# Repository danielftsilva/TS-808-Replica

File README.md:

<h1>TS-808 Replica Project</h1>

<h2>Description</h2>

This repository details my research, design, assembly, and testing of a replica of the iconic TS-808 distortion pedal.

<h2>🎸 Project Summary:</h2>

<b>Research:</b> Studied the original TS-808 design and gathered all necessary information.

<b>Design:</b> Created PCB schematics and layout using KiCad.

<b>Assembly:</b> Purchased components and assembled the PCB.

<b>Testing:</b> Tested to ensure functionality (the most fun part).

<b>Documentation:</b> Photos and documents of every step of the process.

<h2>⚡ Implementation Details:</h2>

<b>From Reference Schematic to PCB:</b>

- The design is rooted in the [reference schematic](https://github.com/danielftsilva/TS-808-Replica/blob/main/KiCad%20Project/ts-808_original%20reference_circuit.jpg) for the Ibanez TS-808 circuit, capturing the preamp, diode clipping, and tone control sections. This schematic outlines the signal path - from the initial buffering of the input signal through the op-amp stages to the final output drive.

- The "heart" of this circuit is the [RC4558](https://www.ti.com/lit/ds/symlink/rc4558.pdf?ts=1740038954763&ref_url=https%253A%252F%252Fwww.google.com%252F), a dual OP-AMP. It handles both the input buffering and the overdrive stages. It's low-noise gives you a warm, smooth distortion (the main and sought-out characteristic of this pedal!). Also, the dual configuration allows one section to amplify the signal while the other handles its tone.

- Here you can see the [final circuit schematic](https://github.com/danielftsilva/TS-808-Replica/blob/main/KiCad%20Project/Main%20Circuit.png).

<!-- modifications -->
<!-- There were a few modifications done on the circuit, namely:

1. Asymmetric clipping: two diodes placed in series (D1 and D2) introduce asymmetric clipping and produce a more "tube-like" distortion with a more dynamic response;

2. Clipper change: a lever switch (SPST) allows selection between different clipping devices - in this case between silicon diodes (1N914) and regular red LEDs. This gives us two distortion textures in the same circuit, providing more flexibility in shaping the pedal's sound;

3. AMZ Fat Modification

Change: A switch is added to bypass capacitor C3.

Impact: Increases boost and enhances bass response, resulting in a fuller and richer tone.

4. Keeley 808 Reissue Modifications

Changes:

Replace R6 (4.7kΩ) with a 2.4kΩ resistor.

Replace R7 (51kΩ) with a 20kΩ resistor.

Replace C3 (0.047µF) with a 0.1µF capacitor.

Replace C9 (0.22µF) with a 0.18µF capacitor.

Impact: Improves bass response and increases distortion at higher drive settings, enhancing the pedal's versatility.

5. Diode Lift Modification

Change: Uses an on-off-on SPDT toggle switch for the diode clipper selector, allowing diode clippers to be lifted from the feedback loop.

Impact: Enables the pedal to function as a clean booster when the diodes are lifted. At high drive settings, this may introduce a more aggressive, raw distortion.

6. Expensive Boutique Modifications

Changes:

Implements diode switching with a diode lift option.

Applies asymmetric clipping modification.

Replaces the Drive potentiometer with a 1MΩ logarithmic pot.

Impact: Aims to replicate high-end boutique overdrive pedals, providing increased gain and a unique tonal character.

Build Information

The project is built on a PCB based on the original TS-808 schematic, with additional wiring for the modifications.

High-quality components were used to maintain signal integrity and reliability.

The modifications were inspired by well-known guitar pedal modders and adapted to suit a wide range of playing styles. -->
<!-- -->

- The [placement afterwards](https://github.com/danielftsilva/TS-808-Replica/blob/main/KiCad%20Project/Layout/Placement_2.png) was super simple and straighforward - just had to pay attention to the distance between the components (I used a [1mm track width](https://github.com/danielftsilva/TS-808-Replica/blob/main/KiCad%20Project/Layout/tracks_2.png) as it was more than enough for this project).

- This PCB is comprised of a simple 2-layer stackup ([main design rules here](https://github.com/danielftsilva/TS-808-Replica/blob/main/KiCad%20Project/production/JLCPCB_KiCad_board_setup_1.png)) - the components occupy the top layer (even though they are all THT). Therefore, in order to not this layer, all the tracks were routed on the bottom layer, which can be seen here in the [final layout](https://github.com/danielftsilva/TS-808-Replica/blob/main/KiCad%20Project/Layout/Layout.png).

<b>Component Selection and Soldering:</b>

- The components selected are listed in the [BOM file](https://github.com/danielftsilva/TS-808-Replica/blob/main/BOM/ts_808_generated_BOM.xlsx).

- The [PCB](https://github.com/danielftsilva/TS-808-Replica/blob/main/Assembly/PCB_unpopulated.jpg) was ordered from [JLC PCB](https://github.com/danielftsilva/TS-808-Replica/blob/main/KiCad%20Project/production/JLC_PCB_order.png) and it measures 75.00mm x 52.00mm. It was intended to fit inside a 127.00mm x 76.250mm [Hammond enclosure](https://eu.mouser.com/ProductDetail/Hammond-Manufacturing/1411NU?qs=k5YXvLLCsLFkprr1MgbOww%3D%3D).

- Here you can see the [final populated PCB](https://github.com/danielftsilva/TS-808-Replica/blob/main/Assembly/PCB_populated.jpg).

<b>Testing and Troubleshooting:</b>

- I started by assembling the populated PCB and external components with the help of a breadboard. Then, I powered up the pedal to check for proper voltage levels and continuity across the circuit using a multimeter.

- I used [this troubleshooting guide](https://github.com/danielftsilva/TS-808-Replica/blob/main/Tests/TROUBLESHOOTING%20CHART.jpg) for my [check](https://github.com/danielftsilva/TS-808-Replica/blob/main/Tests/schematic%20component%20test%20check.png). It is very useful to diagnose common issues like misoriented components or cold solder joints.

- *Note: if you encounter audible noise on this breadboard setup, do not worry too much - it is much likely due to the lack of proper grounding. Also, using somewhat long prototyping cables like I used can help pickup random noise! This should be solved once you assemble everything inside the metal enclosure.*

- Here is [video footage of me testing the complete circuit](https://github.com/danielftsilva/TS-808-Replica/blob/main/Tests/Test.mov), using a breadboard - troubleshooting phase.

- Here you can see the [final assembled pedal turned on](https://github.com/danielftsilva/TS-808-Replica/blob/main/Tests/Pedal_ON_2.jpeg), using a 9V, 1A AC/DC adapter.

- and video footage (Test.mov), ensures every aspect of the build is verified.

<b>Mechanical Integration:</b>

- Once populated, the PCB was mounted within the pedal's enclosure. Let the importance of proper mechanical support be stressed! This is to minimize vibration and potential interference.

- The external components - jacks, switches and potentiometers - [were then connected](https://github.com/danielftsilva/TS-808-Replica/blob/main/Assembly/Pedal_assembled_1.jpeg). Wire routing is crucial to prevent noise pickup.

- The enclosure was then prepared for final assembly, including optional steps: in my case, I drilled the [necessary holes](https://github.com/danielftsilva/TS-808-Replica/blob/main/Assembly/Pedal_assembled_2.jpeg) and sanded them with #220 grit sandpaper - this is recommended before painting to ensure more durability. [I painted it green](https://github.com/danielftsilva/TS-808-Replica/blob/main/Assembly/Pedal_assembled_3.jpeg).

<h2>🛠️ Tools Needed:</h2>

- Soldering iron and stand

- Solder

- Small side cutters and wire strippers

- Hookup wire (24 gauge stranded, insulated)

- Multimeter

- Magnifying glass (optional)

- Close-in bright light (desk lamp)

*Credits to [General Guitar Gadgets](https://generalguitargadgets.com/effects-projects/distortion/tube-screamer/).*

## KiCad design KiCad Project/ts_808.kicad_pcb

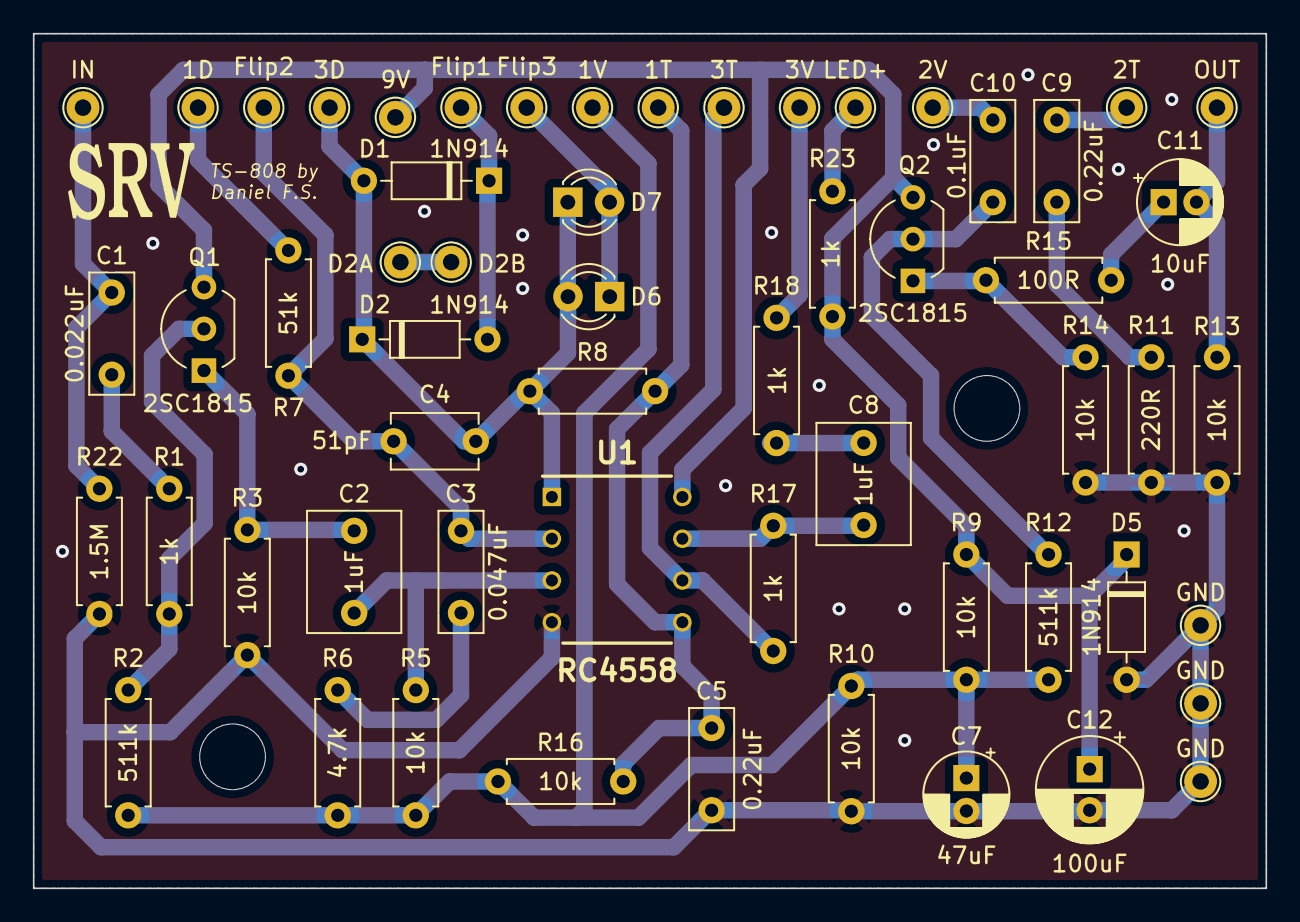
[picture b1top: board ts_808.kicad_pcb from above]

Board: 2 copper layers, 75.0 x 52.0 mm, 60 parts (0 on the bottom side), 28 nets.

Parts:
1D: 1D; TestPoint_THTPad_D2.0mm_Drill1.0mm
1T: 1T; TestPoint_THTPad_D2.0mm_Drill1.0mm
1V: 1V; TestPoint_THTPad_D2.0mm_Drill1.0mm
2T: 2T; TestPoint_THTPad_D2.0mm_Drill1.0mm
2V: 2V; TestPoint_THTPad_D2.0mm_Drill1.0mm
3D: 3D; TestPoint_THTPad_D2.0mm_Drill1.0mm
3T: 3T; TestPoint_THTPad_D2.0mm_Drill1.0mm
3V: 3V; TestPoint_THTPad_D2.0mm_Drill1.0mm
9V: 9V; TestPoint_THTPad_D2.0mm_Drill1.0mm
C1: 0.022uF; C_Rect_L7.2mm_W2.5mm_P5.00mm_FKS2_FKP2_MKS2_MKP2
C2, C8: 1uF; C_Rect_L7.2mm_W5.5mm_P5.00mm_FKS2_FKP2_MKS2_MKP2
C3: 0.047uF; C_Rect_L7.2mm_W2.5mm_P5.00mm_FKS2_FKP2_MKS2_MKP2
C4: 51pF; C_Disc_D5.1mm_W3.2mm_P5.00mm
C5, C9: 0.22uF; C_Rect_L7.2mm_W2.5mm_P5.00mm_FKS2_FKP2_MKS2_MKP2
C7: 47uF; CP_Radial_D5.0mm_P2.00mm
C10: 0.1uF; C_Rect_L7.2mm_W2.5mm_P5.00mm_FKS2_FKP2_MKS2_MKP2
C11: 10uF; CP_Radial_D5.0mm_P2.00mm
C12: 100uF; CP_Radial_D6.3mm_P2.50mm
D1, D2, D5: 1N914; D_DO-35_SOD27_P7.62mm_Horizontal
D2A: D2ab_1; TestPoint_THTPad_D2.0mm_Drill1.0mm
D2B: D2ab_2; TestPoint_THTPad_D2.0mm_Drill1.0mm
D6, D7: LED_Red; LED_D3.0mm
Flip1: Flip_SW_1; TestPoint_THTPad_D2.0mm_Drill1.0mm
Flip2: Flip_SW_2; TestPoint_THTPad_D2.0mm_Drill1.0mm
Flip3: Flip_SW_3; TestPoint_THTPad_D2.0mm_Drill1.0mm
GND: GND_1; TestPoint_THTPad_D2.0mm_Drill1.0mm
GND#2: GND_2; TestPoint_THTPad_D2.0mm_Drill1.0mm
GND#3: GND_3; TestPoint_THTPad_D2.0mm_Drill1.0mm
H1, H2: MountingHole; MountingHole_4mm
IN: In; TestPoint_THTPad_D2.0mm_Drill1.0mm
LED+: LED_ind+; TestPoint_THTPad_D2.0mm_Drill1.0mm
OUT: Out; TestPoint_THTPad_D2.0mm_Drill1.0mm
Q1, Q2: 2SC1815; TO-92_Inline_Wide
R1, R8, R17, R18, R23: 1k; R_Axial_DIN0207_L6.3mm_D2.5mm_P7.62mm_Horizontal
R2, R12: 511k; R_Axial_DIN0207_L6.3mm_D2.5mm_P7.62mm_Horizontal
R3, R5, R9, R10, R13, R14, R16: 10k; R_Axial_DIN0207_L6.3mm_D2.5mm_P7.62mm_Horizontal
R6: 4.7k; R_Axial_DIN0207_L6.3mm_D2.5mm_P7.62mm_Horizontal
R7: 51k; R_Axial_DIN0207_L6.3mm_D2.5mm_P7.62mm_Horizontal
R11: 220R; R_Axial_DIN0207_L6.3mm_D2.5mm_P7.62mm_Horizontal
R15: 100R; R_Axial_DIN0207_L6.3mm_D2.5mm_P7.62mm_Horizontal
R22: 1.5M; R_Axial_DIN0207_L6.3mm_D2.5mm_P7.62mm_Horizontal
U1: RC4558; RC4558P_PDIP_8

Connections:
GNDREF: C5.1, C7.2, C12.2, D5.2 (A), GND.1, GND#2.1, GND#3.1, R3.1, R10.1, R11.2, R13.1, R14.1, R22.1, U1.4 (V-)
unnamed: C1.1, IN.1, R22.2
unnamed: C1.2, R1.1
unnamed: C2.1, Q1.1 (E), R3.2
unnamed: C2.2, R5.2, U1.3 (+)
unnamed: C3.1, R6.2
unnamed: C3.2, C4.1, Flip2.1, R7.1, U1.2 (-)
unnamed: 3D.1, C4.2, D1.2 (A), D2.1 (K), D6.2 (A), D7.1 (K), R8.1, U1.1
unnamed: 1T.1, C5.2, R8.2, R16.2, U1.5 (+)
unnamed: 1V.1, C7.1, R2.2, R5.1, R6.1, R9.2, R10.2, R12.1, R16.1
unnamed: C8.1, R17.2, U1.7
unnamed: C8.2, R18.1
unnamed: 2T.1, C9.1
unnamed: C9.2, R11.1
unnamed: 2V.1, C10.1
unnamed: C10.2, Q2.2 (B), R12.2
unnamed: C11.1, R15.2
unnamed: C11.2, OUT.1, R13.2
unnamed: 9V.1, C12.1, D5.1 (K), Q1.3 (C), Q2.3 (C), R9.1, R23.2, U1.8 (V+)
unnamed: D1.1 (K), D2.2 (A), Flip1.1
unnamed: D6.1 (K), D7.2 (A), Flip3.1
unnamed: Q1.2 (B), R1.2, R2.1
unnamed: Q2.1 (E), R14.2, R15.1
unnamed: 1D.1, R7.2
unnamed: 3T.1, R17.1, U1.6 (-)
unnamed: 3V.1, R18.2
unnamed: LED+.1, R23.1
unnamed: D2A.1, D2B.1

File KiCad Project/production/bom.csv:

Designator,Footprint,Quantity,Value,LCSC Part #
C1,C_Rect_L7.2mm_W2.5mm_P5.00mm_FKS2_FKP2_MKS2_MKP2,1,0.022uF,
C10,C_Rect_L7.2mm_W2.5mm_P5.00mm_FKS2_FKP2_MKS2_MKP2,1,0.1uF,
C11,CP_Radial_D5.0mm_P2.00mm,1,10uF,
C12,CP_Radial_D6.3mm_P2.50mm,1,100uF,
"C2, C8",C_Rect_L7.2mm_W5.5mm_P5.00mm_FKS2_FKP2_MKS2_MKP2,2,1uF,
C3,C_Rect_L7.2mm_W2.5mm_P5.00mm_FKS2_FKP2_MKS2_MKP2,1,0.047uF,
C4,C_Disc_D5.1mm_W3.2mm_P5.00mm,1,51pF,
"C5, C9",C_Rect_L7.2mm_W2.5mm_P5.00mm_FKS2_FKP2_MKS2_MKP2,2,0.22uF,
C7,CP_Radial_D5.0mm_P2.00mm,1,47uF,
"D1, D2, D5",D_DO-35_SOD27_P7.62mm_Horizontal,3,1N914,
"D6, D7",LED_D3.0mm,2,LED_Red,
"H1, H2",MountingHole_4mm,2,MountingHole,
"Q1, Q2",TO-92_Inline,2,2SC1815,
"R1, R17, R18, R23, R8",R_Axial_DIN0207_L6.3mm_D2.5mm_P7.62mm_Horizontal,5,1k,
"R10, R13, R14, R16, R3, R5, R9",R_Axial_DIN0207_L6.3mm_D2.5mm_P7.62mm_Horizontal,7,10k,
R11,R_Axial_DIN0207_L6.3mm_D2.5mm_P7.62mm_Horizontal,1,220R,
"R12, R2",R_Axial_DIN0207_L6.3mm_D2.5mm_P7.62mm_Horizontal,2,511k,
R15,R_Axial_DIN0207_L6.3mm_D2.5mm_P7.62mm_Horizontal,1,100R,
R22,R_Axial_DIN0207_L6.3mm_D2.5mm_P7.62mm_Horizontal,1,1.5M,
R6,R_Axial_DIN0207_L6.3mm_D2.5mm_P7.62mm_Horizontal,1,4.7k,
R7,R_Axial_DIN0207_L6.3mm_D2.5mm_P7.62mm_Horizontal,1,51k,
TP1,TestPoint_THTPad_D2.0mm_Drill1.0mm,1,In,
TP10,TestPoint_THTPad_D2.0mm_Drill1.0mm,1,1D,
TP11,TestPoint_THTPad_D2.0mm_Drill1.0mm,1,3D,
TP12,TestPoint_THTPad_D2.0mm_Drill1.0mm,1,Flip_SW_1,
TP13,TestPoint_THTPad_D2.0mm_Drill1.0mm,1,1T,
TP14,TestPoint_THTPad_D2.0mm_Drill1.0mm,1,2T,
TP15,TestPoint_THTPad_D2.0mm_Drill1.0mm,1,3T,
TP16,TestPoint_THTPad_D2.0mm_Drill1.0mm,1,3V,
TP17,TestPoint_THTPad_D2.0mm_Drill1.0mm,1,2V,
TP18,TestPoint_THTPad_D2.0mm_Drill1.0mm,1,1V,
TP19,TestPoint_THTPad_D2.0mm_Drill1.0mm,1,Out,
TP2,TestPoint_THTPad_D2.0mm_Drill1.0mm,1,9V,
TP20,TestPoint_THTPad_D2.0mm_Drill1.0mm,1,Flip_SW_2,
TP23,TestPoint_THTPad_D2.0mm_Drill1.0mm,1,GND_2,
TP3,TestPoint_THTPad_D2.0mm_Drill1.0mm,1,GND_3,
TP4,TestPoint_THTPad_D2.0mm_Drill1.0mm,1,GND_1,
TP5,TestPoint_THTPad_D2.0mm_Drill1.0mm,1,LED_ind+,
TP7,TestPoint_THTPad_D2.0mm_Drill1.0mm,1,Flip_SW_3,
TP8,TestPoint_THTPad_D2.0mm_Drill1.0mm,1,D2ab_1,
TP9,TestPoint_THTPad_D2.0mm_Drill1.0mm,1,D2ab_2,
U1,RC4558P_PDIP_8,1,RC4558,

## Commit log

2025-02-18 Full project added
2025-02-18 Full project commit
2025-02-20 pulled readme
2025-02-20 readme
2025-02-21 KiCad spark libraries added
